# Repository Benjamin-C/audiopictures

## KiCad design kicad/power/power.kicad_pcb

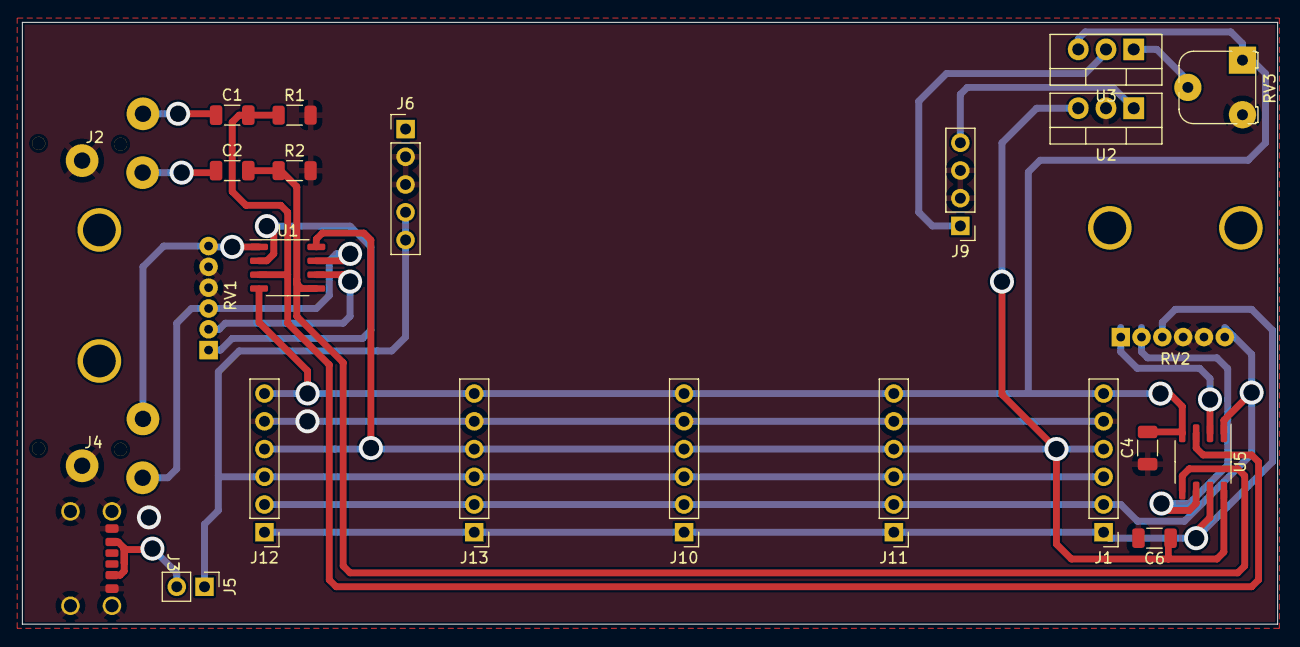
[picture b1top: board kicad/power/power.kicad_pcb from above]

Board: 2 copper layers, 114.9 x 55.1 mm, 24 parts (0 on the bottom side), 20 nets.

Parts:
C1, C2: 1u; C_1206_3216Metric
C4, C6: C; C_1206_3216Metric
J1, J10, J11, J12, J13: Conn_01x06; PinHeader_1x06_P2.54mm_Vertical
J2, J4: AudioJack3; audio_jack
J3: USB_C_Receptacle; usb_footprint
J5: Conn_01x02_Male; PinHeader_1x02_P2.54mm_Vertical
J6: Conn_01x05_Male; PinHeader_1x05_P2.54mm_Vertical
J9: Conn_01x04_Male; PinHeader_1x04_P2.54mm_Vertical
R1, R2: 100k; R_1206_3216Metric
RV1, RV2: R_Potentiometer_Dual_Separate; volume-pot
RV3: R_Potentiometer; Potentiometer_Runtron_RM-065_Vertical
U1: LM4565F-GE2; SOP-8_3.9x4.9mm_P1.27mm
U2: LM7812_TO220; TO-220-3_Vertical
U3: LM337_TO220; TO-220-3_Vertical
U5: LF353DR; SOP-8_3.9x4.9mm_P1.27mm

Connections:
+5V: J1.3, J5.1, J6.4, J6.5, J10.3, J11.3, J12.3, J13.3
+12V: C6.1, J1.4, J10.4, J11.4, J12.4, J13.4, U1.8 (V+), U2.3 (VO), U5.8 (V+)
+15V: J9.4, U2.1 (VI)
-12V: C4.2, J1.6, J10.6, J11.6, J12.6, J13.6, RV3.1, U1.4 (V-), U3.3 (VO), U5.4 (V-)
-15V: J9.1, U3.2 (VI)
GND: C4.1, C6.2, J1.5, J2.S, J3.A12 (GND), J3.B12 (GND), J3.S1 (SHIELD), J4.S, J6.2, J6.3, J9.2, J9.3, J10.5, J11.5, J12.5, J13.5, R1.2, R2.2, RV1.3, RV1.6, RV2.3, RV2.6, RV3.3, U2.2 (GND)
unnamed: C1.1, J2.T
unnamed: C2.1, J2.R
unnamed: J3.A9 (VBUS), J3.B9 (VBUS), J5.2
unnamed: J4.R, RV1.5, U1.7
unnamed: J4.T, RV1.2, U1.1
unnamed: RV1.1, U1.2 (-)
unnamed: RV1.4, U1.6 (-)
unnamed: RV2.1, U5.2 (-)
unnamed: RV2.4, U5.6 (-)
unnamed: RV3.2, U3.1 (ADJ)
audio_in_L: C1.2, R1.1, U1.3 (+), U5.3 (+)
audio_in_R: C2.2, R2.1, U1.5 (+), U5.5 (+)
audio_lefT: J1.2, J10.2, J11.2, J12.2, J13.2, RV2.2, U5.1
audio_right: J1.1, J10.1, J11.1, J12.1, J13.1, RV2.5, U5.7

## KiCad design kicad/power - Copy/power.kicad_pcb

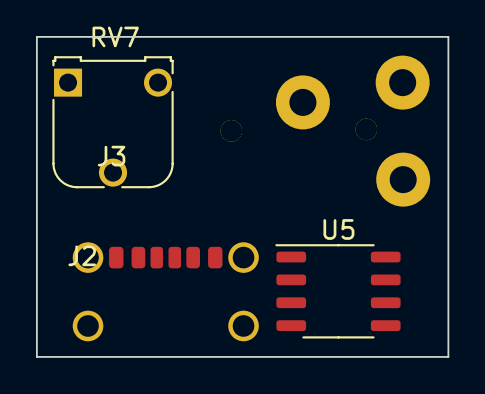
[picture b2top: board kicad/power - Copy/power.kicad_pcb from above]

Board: 2 copper layers, 22.9 x 17.8 mm, 4 parts (0 on the bottom side), 4 nets, no tracks yet.

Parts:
J2: AudioJack3; audio_jack
J3: USB_C_Receptacle; usb_footprint
RV7: 2k2; Potentiometer_Runtron_RM-065_Vertical
U5: LF353DR; SOP-8_3.9x4.9mm_P1.27mm

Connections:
+5V: J3.A9 (VBUS), J3.B9 (VBUS)
GND: J3.A12 (GND), J3.B12 (GND), J3.S1 (SHIELD), RV7.3
unnamed: RV7.1, U5.2 (-)
audio_lefT: RV7.2, U5.1

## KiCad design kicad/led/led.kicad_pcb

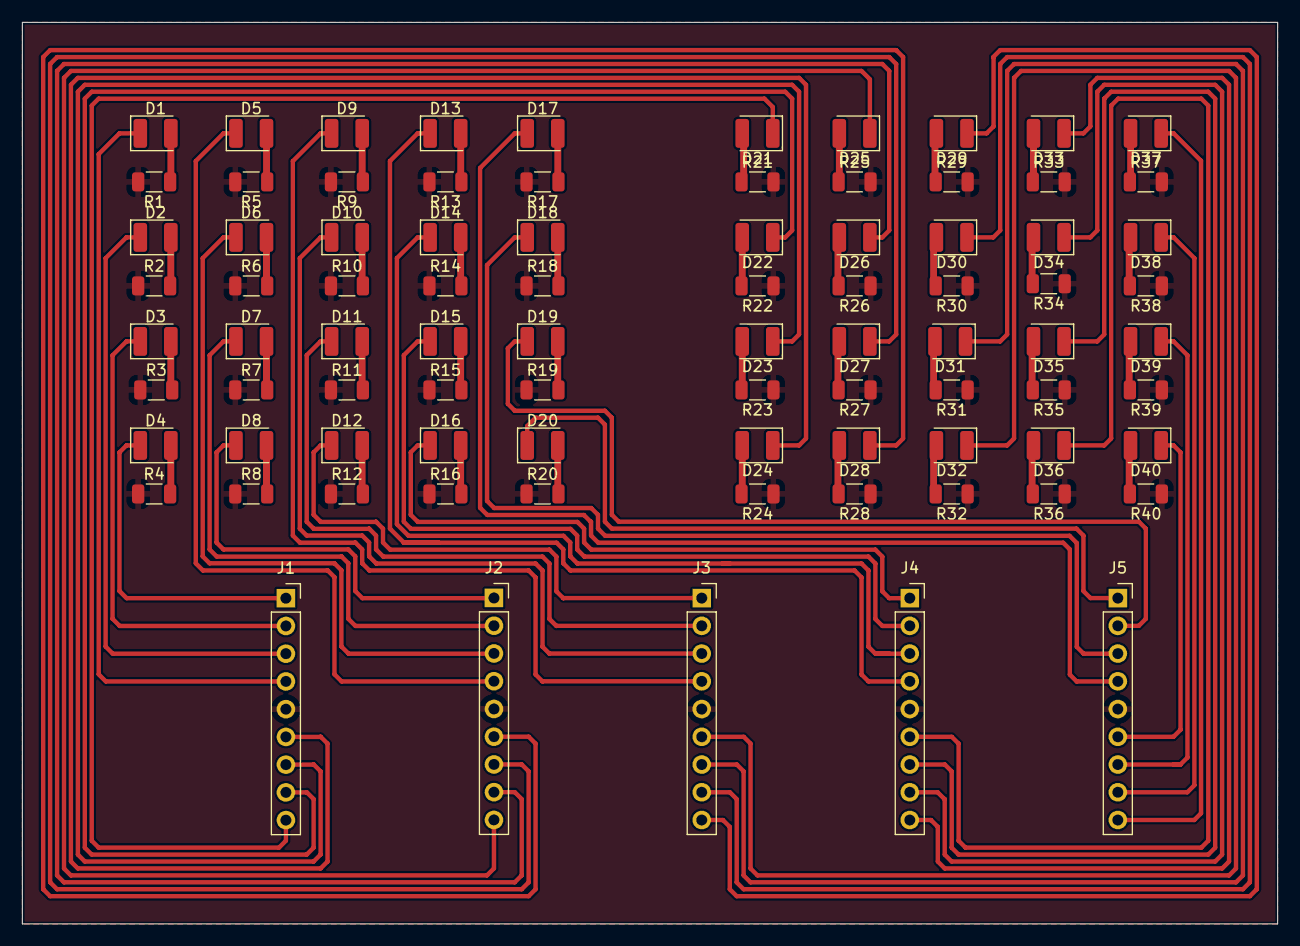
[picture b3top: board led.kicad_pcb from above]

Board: 2 copper layers, 114.9 x 82.5 mm, 85 parts (0 on the bottom side), 81 nets.

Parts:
D1, D5, D9, D13, D17, D21, D25, D29, D33, D37: ORANGE; LED_1210_3225Metric
D2, D6, D10, D14, D18, D22, D26, D30, D34, D38: YELLOW; LED_1210_3225Metric
D3, D7, D11, D15, D19, D23, D27, D31, D35, D39: GREEN; LED_1210_3225Metric
D4, D8, D12, D16, D20, D24, D28, D32, D36, D40: BLUE; LED_1210_3225Metric
J1, J2, J3, J4, J5: Conn_01x09_Male; PinSocket_1x09_P2.54mm_Vertical
R1, R2, R3, R4, R5, R6, R7, R8, R9, R10, R11, R12, R13, R14, R15, R16, R17, R18, R19, R20, R21, R22, R23, R24, R25, R26, R27, R28, R29, R30, R31, R32, R33, R34, R35, R36, R37, R38, R39, R40: R; R_1206_3216Metric

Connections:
+5V: J1.5, J2.5, J3.5, J4.5, J5.5, R1.2, R2.1, R3.1, R4.1, R5.2, R6.1, R7.1, R8.1, R9.2, R10.1, R11.1, R12.1, R13.2, R14.1, R15.1, R16.1, R17.2, R18.1, R19.1, R20.1, R21.2, R22.1, R23.1, R24.1, R25.2, R26.1, R27.1, R28.1, R29.2, R30.1, R31.1, R32.1, R33.2, R34.1, R35.1, R36.1, R37.2, R38.1, R39.1, R40.1
unnamed: D1.1 (K), J1.4
unnamed: D1.2 (A), R1.1
unnamed: D2.1 (K), J1.3
unnamed: D2.2 (A), R2.2
unnamed: D3.1 (K), J1.2
unnamed: D3.2 (A), R3.2
unnamed: D4.1 (K), J1.1
unnamed: D4.2 (A), R4.2
unnamed: D5.1 (K), J2.4
unnamed: D5.2 (A), R5.1
unnamed: D6.1 (K), J2.3
unnamed: D6.2 (A), R6.2
unnamed: D7.1 (K), J2.2
unnamed: D7.2 (A), R7.2
unnamed: D8.1 (K), J2.1
unnamed: D8.2 (A), R8.2
unnamed: D9.1 (K), J3.4
unnamed: D9.2 (A), R9.1
unnamed: D10.1 (K), J3.3
unnamed: D10.2 (A), R10.2
unnamed: D11.1 (K), J3.2
unnamed: D11.2 (A), R11.2
unnamed: D12.1 (K), J3.1
unnamed: D12.2 (A), R12.2
unnamed: D13.1 (K), J4.4
unnamed: D13.2 (A), R13.1
unnamed: D14.1 (K), J4.3
unnamed: D14.2 (A), R14.2
unnamed: D15.1 (K), J4.2
unnamed: D15.2 (A), R15.2
unnamed: D16.1 (K), J4.1
unnamed: D16.2 (A), R16.2
unnamed: D17.1 (K), J5.4
unnamed: D17.2 (A), R17.1
unnamed: D18.1 (K), J5.3
unnamed: D18.2 (A), R18.2
unnamed: D19.1 (K), J5.2
unnamed: D19.2 (A), R19.2
unnamed: D20.1 (K), J5.1
unnamed: D20.2 (A), R20.2
unnamed: D21.1 (K), J1.9
unnamed: D21.2 (A), R21.1
unnamed: D22.1 (K), J1.8
unnamed: D22.2 (A), R22.2
unnamed: D23.1 (K), J1.7
unnamed: D23.2 (A), R23.2
unnamed: D24.1 (K), J1.6
unnamed: D24.2 (A), R24.2
unnamed: D25.1 (K), J2.9
unnamed: D25.2 (A), R25.1
unnamed: D26.1 (K), J2.8
unnamed: D26.2 (A), R26.2
unnamed: D27.1 (K), J2.7
unnamed: D27.2 (A), R27.2
unnamed: D28.1 (K), J2.6
unnamed: D28.2 (A), R28.2
unnamed: D29.1 (K), J3.9
unnamed: D29.2 (A), R29.1
unnamed: D30.1 (K), J3.8
unnamed: D30.2 (A), R30.2
unnamed: D31.1 (K), J3.7
unnamed: D31.2 (A), R31.2
unnamed: D32.1 (K), J3.6
unnamed: D32.2 (A), R32.2
unnamed: D33.1 (K), J4.9
unnamed: D33.2 (A), R33.1
unnamed: D34.1 (K), J4.8
unnamed: D34.2 (A), R34.2
unnamed: D35.1 (K), J4.7
unnamed: D35.2 (A), R35.2
unnamed: D36.1 (K), J4.6
unnamed: D36.2 (A), R36.2
unnamed: D37.1 (K), J5.9
unnamed: D38.1 (K), J5.8
unnamed: D38.2 (A), R38.2
unnamed: D39.1 (K), J5.7
unnamed: D39.2 (A), R39.2
unnamed: D40.1 (K), J5.6
unnamed: D40.2 (A), R40.2
unnamed: D37.2 (A), R37.1

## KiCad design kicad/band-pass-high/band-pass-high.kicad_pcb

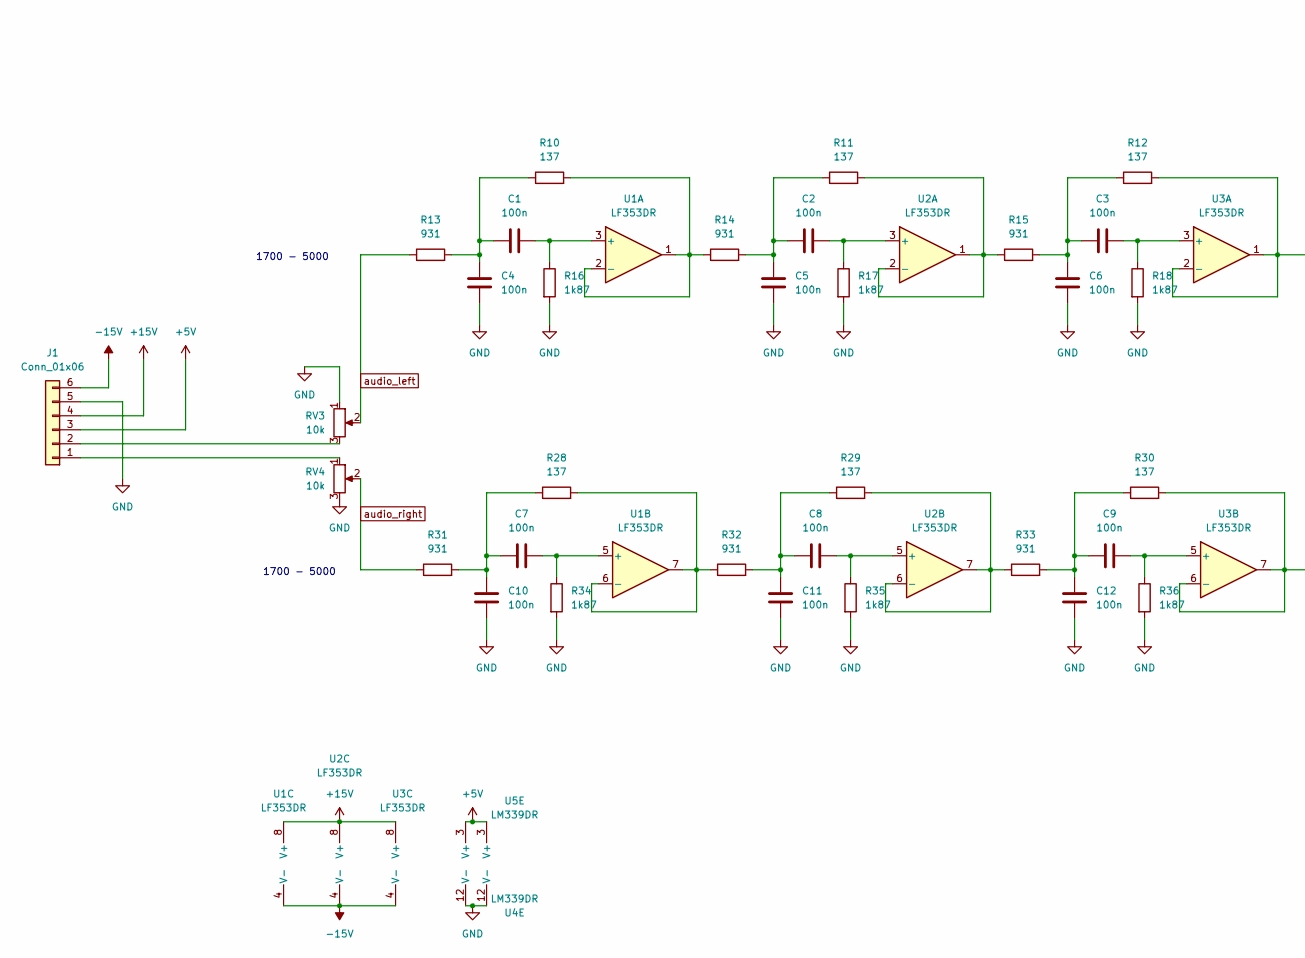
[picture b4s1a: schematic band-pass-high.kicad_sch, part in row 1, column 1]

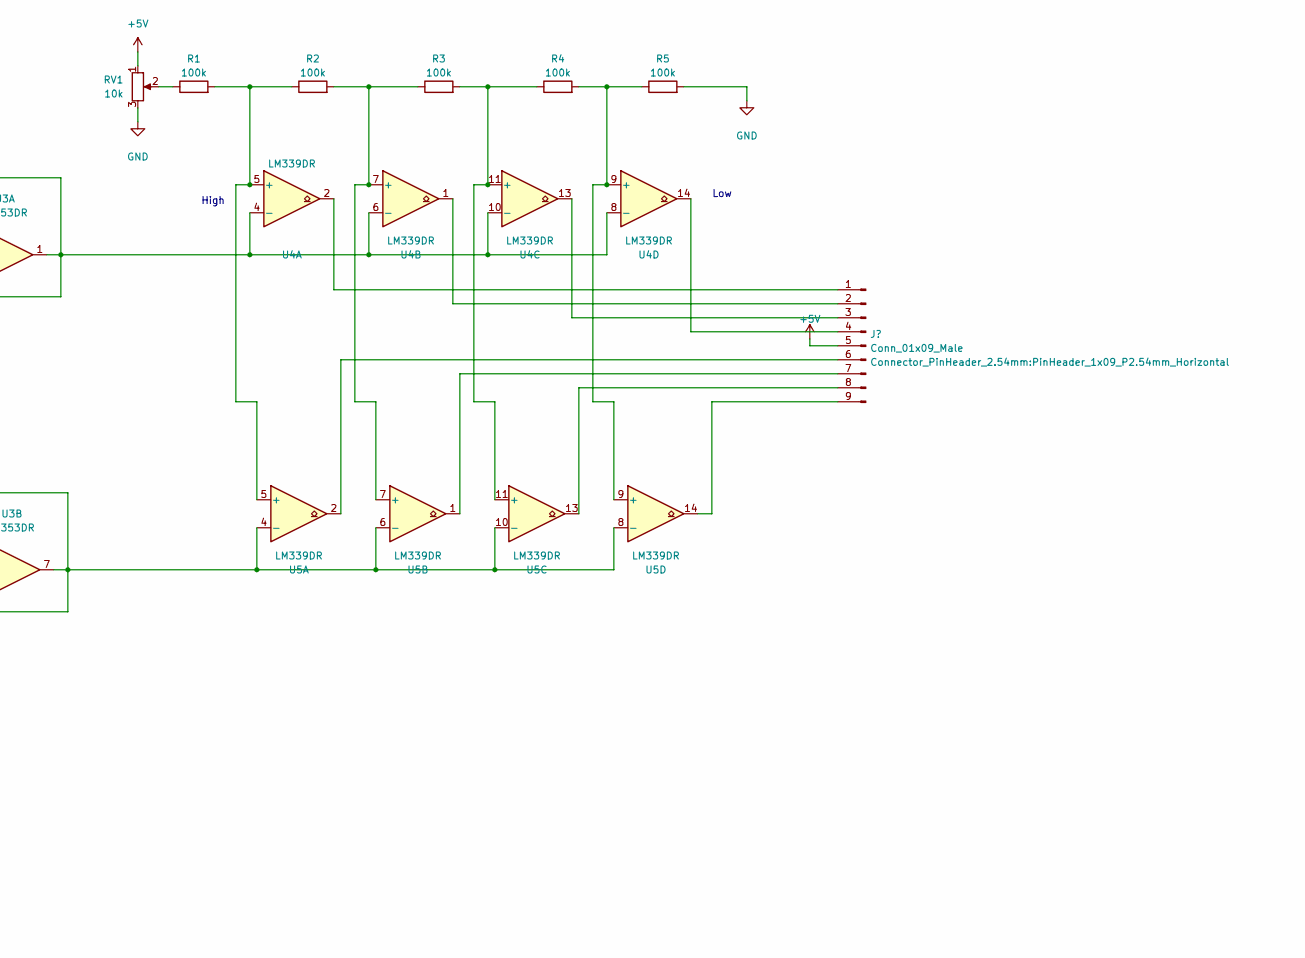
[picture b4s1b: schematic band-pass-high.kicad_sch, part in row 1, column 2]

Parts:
C1, C2, C3, C4, C5, C6, C7, C8, C9, C10, C11, C12: 100n; C_1206_3216Metric
J1: Conn_01x06; PinHeader_1x06_P2.54mm_Horizontal
R1, R2, R3, R4, R5: 100k; R_1206_3216Metric
R10, R11, R12, R28, R29, R30: 137; R_1206_3216Metric
R13, R14, R15, R31, R32, R33: 931; R_1206_3216Metric
R16, R17, R18, R34, R35, R36: 1k87; R_1206_3216Metric
RV1, RV3, RV4: 10k; Potentiometer_Runtron_RM-065_Vertical
U1, U2, U3: LF353DR; SOIC-8_3.9x4.9mm_P1.27mm
U4, U5: LM339DR; SO-14_3.9x8.65mm_P1.27mm

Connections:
+5V: J1.3, RV1.1, U4.3 (V+), U5.3 (V+); also elsewhere on the board
+15V: J1.4, U1.8 (V+), U2.8 (V+), U3.8 (V+)
-15V: J1.6, U1.4 (V-), U2.4 (V-), U3.4 (V-)
GND: C4.2, C5.2, C6.2, C10.2, C11.2, C12.2, J1.5, R5.2, R16.2, R17.2, R18.2, R34.2, R35.2, R36.2, RV1.3, RV3.1, RV4.3, U4.12 (V-), U5.12 (V-)
unnamed: C1.2, R16.1, U1.3 (+)
unnamed: C2.2, R17.1, U2.3 (+)
unnamed: C3.2, R18.1, U3.3 (+)
unnamed: C1.1, C4.1, R10.1, R13.2
unnamed: C2.1, C5.1, R11.1, R14.2
unnamed: C3.1, C6.1, R12.1, R15.2
unnamed: C7.2, R34.1, U1.5 (+)
unnamed: C8.2, R35.1, U2.5 (+)
unnamed: C9.2, R36.1, U3.5 (+)
unnamed: C7.1, C10.1, R28.1, R31.2
unnamed: C8.1, C11.1, R29.1, R32.2
unnamed: C9.1, C12.1, R30.1, R33.2
unnamed: J1.1, RV4.1
unnamed: J1.2, RV3.3
unnamed: R1.1, RV1.2
unnamed: R1.2, R2.1, U4.5 (+), U5.5 (+)
unnamed: R2.2, R3.1, U4.7 (+), U5.7 (+)
unnamed: R3.2, R4.1, U4.11 (+), U5.11 (+)
unnamed: R4.2, R5.1, U4.9 (+), U5.9 (+)
unnamed: R10.2, R14.1, U1.1, U1.2 (-)
unnamed: R11.2, R15.1, U2.1, U2.2 (-)
unnamed: R12.2, U3.1, U3.2 (-), U4.4 (-), U4.6 (-), U4.8 (-), U4.10 (-)
unnamed: R28.2, R32.1, U1.6 (-), U1.7
unnamed: R29.2, R33.1, U2.6 (-), U2.7
unnamed: R30.2, U3.6 (-), U3.7, U5.4 (-), U5.6 (-), U5.8 (-), U5.10 (-)
unnamed 29: U4.1; also elsewhere on the board
unnamed 30: U4.2; also elsewhere on the board
unnamed 31: U4.13; also elsewhere on the board
unnamed 32: U4.14; also elsewhere on the board
unnamed 33: U5.1; also elsewhere on the board
unnamed 34: U5.2; also elsewhere on the board
unnamed 35: U5.13; also elsewhere on the board
unnamed 36: U5.14; also elsewhere on the board
audio_left: R13.1, RV3.2
audio_right: R31.1, RV4.2

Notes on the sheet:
High
Low
1700 - 5000

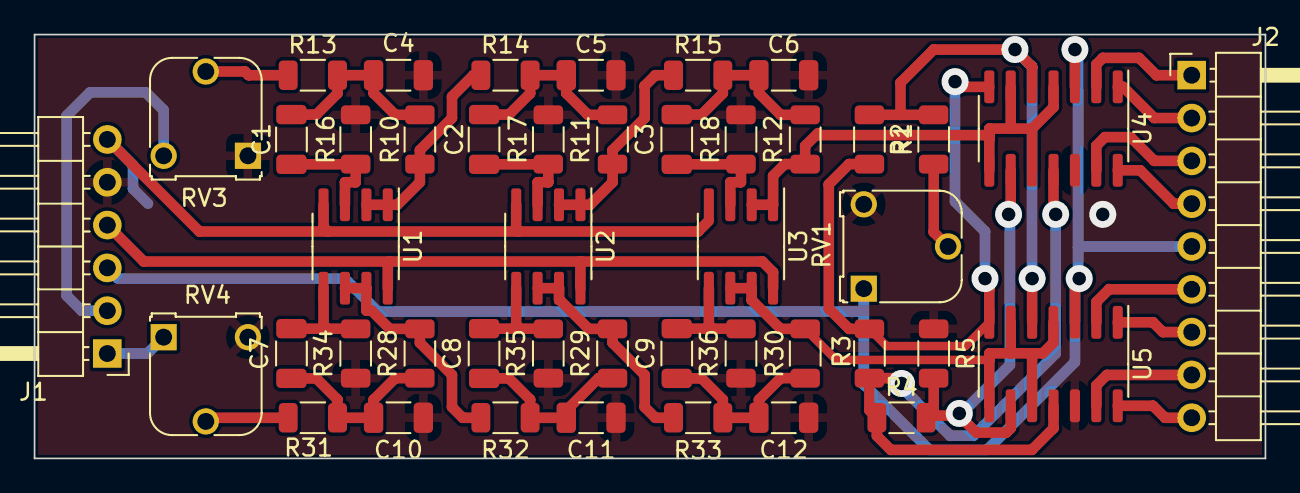
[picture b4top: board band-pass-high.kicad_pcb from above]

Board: 2 copper layers, 73.0 x 25.1 mm, 45 parts (0 on the bottom side), 39 nets.

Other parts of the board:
J2: Conn_01x09_Male; PinHeader_1x09_P2.54mm_Horizontal

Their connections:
+5V: J2.5; also elsewhere on the board
unnamed 29: J2.2; also elsewhere on the board
unnamed 30: J2.1; also elsewhere on the board
unnamed 31: J2.3; also elsewhere on the board
unnamed 32: J2.4; also elsewhere on the board
unnamed 33: J2.7; also elsewhere on the board
unnamed 34: J2.6; also elsewhere on the board
unnamed 35: J2.8; also elsewhere on the board
unnamed 36: J2.9; also elsewhere on the board

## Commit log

2022-04-07 init
2022-04-08 Added some stuffs to plot a thingy
2022-04-14 It is broken
2022-04-15 Fixed frequency and time scales
2022-04-15 Switched to column based processing
2022-04-15 Ignore pycache folder
2022-04-15 GUI test thingy for testing with a GUI
2022-04-15 It might actually work now!
2022-04-15 Added helpful menu
2022-04-15 Cleanup and comments
2022-04-15 Cleanup
2022-04-22 Created filter calc file thingy
2022-04-29 Added bandpass filter
2022-05-01 Added schematic
2022-05-01 Added low pass filter
2022-05-02 Updated schematic
2022-05-02 Added value spreadsheet
2022-05-02 Added high pass filter
2022-05-02 Un-broke things
2022-05-02 Added some new values to schematic
2022-05-06 Added fixed LP values
2022-05-08 Broke circuit into many boards
2022-05-08 Updated gitignore to not include backups
2022-05-08 Made a filter PCB design
2022-05-09 Updated something I think ...
2022-05-09 Found a better way with less vias
2022-05-09 Cleaned up KiCad folder
2022-05-09 Added new KiCad files for other boards
2022-05-09 Updated some power stuff
2022-05-09 Maybe finished LED board I think
2022-05-11 Copied LED board, and made new revision with full connectors, not split
2022-05-11 Made test board
2022-05-13 Power schematic to pcb update
2022-05-14 Made some PCBs
2022-05-14 Did some stuff
2022-05-18 Revision of PCB power circuit
2022-05-18 Power PCB revisions
2022-05-21 Power Newest
2022-05-26 Preparing to maybe do V2 of power
2022-05-26 Made some new stuffs
2022-06-01 Made new power board
2022-06-03 Added scope screenshots
